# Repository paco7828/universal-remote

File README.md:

# Universal Remote

ESP32-based universal infrared remote control with touch screen.
It can **learn** IR signals, **save them to an SD card**, **resend** them,
and transmit **built-in brand codes**.
The entire UI is touch-controlled, featuring scrollable lists and a virtual
keyboard.

---

## Hardware

| Component | Description |
|-----------|-------------|
| MCU | ESP32 (Using FSPI / SPI2 bus) |
| Display | ILI9341 2.4" TFT, 240x320, portrait (rotation 0) |
| Touch | XPT2046 resistive touch, via SPI |
| Storage | MicroSD card |
| IR Transmitter| TSAL6200 |
| IR Receiver | IRM-3638T |

The display and the SD card use **the same SPI bus** (shared MOSI/MISO/CLK),
multiplexed with CS lines. Before sending an IR signal, the code sets `SD_CS` and `TOUCH_CS`
HIGH to avoid bus conflicts.

### Pinout

| Signal | GPIO |
|--------|------|
| TFT CS | 7 |
| TFT RST | 10 |
| TFT DC | 2 |
| TFT MOSI | 6 |
| TFT MISO | 5 |
| TFT CLK | 4 |
| Touch CS | 8 |
| Touch IRQ | 9 |
| SD CS | 3 |
| IR TX | 0 |
| IR RX | 1 |

---

## Dependencies

- **LovyanGFX** - display + touch driver (ILI9341 + XPT2046)
- **IRremoteESP8266** - IR receive / send / decode
- **Preferences** - ESP32 NVS (for saving themes)
- **SD**, **SPI** - Arduino ESP32 core built-in
- **`./IR-codes.h`** - custom header with built-in Pronto Hex codes
  (EPSON and NEC arrays). **Without this, the project will not compile.**

---

## Features

### Signal learning (Receive)

1. `Signal options -> Receive` starts listening mode.
2. The receiver decodes the signal into `decode_results`.
3. The code accepts a **maximum of 3 frames** at once within a signal
   (`MAX_FRAMES = 3`), measuring the pause between them as `gap_ms`.
4. Repeat frames and identical frames are discarded.
5. An `UNKNOWN` (raw) signal is only accepted if it is the **first** frame,
   and contains at least 10 pulses, filtering out noise.
6. The captured signal type is determined automatically:
   - `SIG_VALUE` - known protocol, fixed-length value (e.g., NEC)
   - `SIG_STATE` - AC-like protocols with byte-array states
   - `SIG_RAW` - unknown, raw microsecond array
7. After capture, a **QWERTY keyboard** appears to name the signal
   (max 25 characters, letters + `-`).
8. Saved to the SD card: `/saved-signals/<group>/<name>.txt`.

### Signal sending (Transmit)

- **Saved signals**: `Signal options -> Transmit` -> group list -> signal list -> Send.
  The group is the part of the signal's name before the `-` (e.g., `TV-power` -> `TV` group).
- **Built-in signals**: `Built-in signals` -> brand -> signal -> Send.
- **Long pressing** the `Send` button repeats the signal (except for `SIG_STATE` signals).
- Transmission strategy:
  - `SIG_VALUE`: `irsend.send(protocol, value, bits)` - for RC5/RC6,
    the toggle bit switches automatically on each new press.
  - `SIG_STATE`: `irsend.send(protocol, state, bytes)`.
  - `SIG_RAW`: `irsend.sendRaw(rawData, len, khz)`.
  - If protocol sending returns `false`, but raw data is available, an
    automatic **raw fallback** occurs.
- For multi-frame signals, there is a `gap_ms` pause between frames.

### Built-in signals

The `IRCode` structures declared in `IR-codes.h` store the codes in Pronto Hex format.
The firmware converts them to raw microsecond arrays using the `prontoToRawSignal()`
function and calculates the carrier frequency with `prontoCarrierKHz()`.

Currently, **only these** are available from the UI in the `hardcodedBrands[]` array:

- EPSON
- NEC

(Other brands will only appear if you add them to the array.)

### SD Card Management

- **Info** - total / free / used space + number of saved signal files.
- **Files** - file browser with directory navigation, size display,
  and individual file deletion (`Del` button, **!NO CONFIRMATION MESSAGE!**).
- **Format** - keeps the `/System Volume Information` and `/built-in-signals`
  directories, deletes everything else.
- File list limit: 500 items.

### UI / Themes

Three selectable color themes (persisted in NVS):

- Futuristic Red (default)
- Futuristic Green
- Futuristic Purple

Theme switching is displayed with an animated spreading circle effect.

Other UI features:

- Boot splash: `UNIVERSAL / REMOTE` text for ~2 seconds.
- **Scrollable lists** with a sprite buffer (`LGFX_Sprite`) to prevent flickering.
- **Double tap** on a list item = open.
- **Long hold** on a repeatable button = rapid fire (`REPEAT_INTERVAL = 200 ms`).
- Maximum number of buttons per screen: **30**.
- Button style: corner accents + scanline pattern.

---

## Navigation Structure

```
Main Menu
├── Signal options
│   ├── Transmit  ->  [Group]  ->  [Signal list]  ->  Send
│   └── Receive   ->  Listening... ->  Captured!   ->  Keyboard -> Save
├── Built-in signals
│   └── [Brand]   ->  [Signal list] ->  Send
├── SD Card options
│   ├── Info
│   ├── Files  ->  browser (Up / Back / Del)
│   └── Format ->  Yes, format / Cancel formatting
└── Change theme
    ├── Futuristic Red
    ├── Futuristic Green
    └── Futuristic Purple
```

If SD initialization fails, "SD Card options" disappears from the main menu.

---

## Saved signal file format

**Not binary** - each signal is a simple, line-separated `.txt` file:

```
# UniRemote IR signal
name: TV-power
carrier_khz: 38
frame: 1
gap_ms: 40
protocol: NEC
bits: 32
value: 0x20DF10EF
length: 68
raw: 9000,4500,560,560,...
frame: 2
...
```

Fields per frame:

- `gap_ms` - pause before the next frame (only if there is a next frame)
- `protocol` - name returned by `typeToString()`
- `bits` - number of bits for `SIG_VALUE`, bytes×8 for `SIG_STATE`
- `value` - hex value (`SIG_VALUE`)
- `bytes` - space-separated hex bytes (`SIG_STATE`)
- `length` + `raw` - raw microsecond array (always saved if available)

When loading the file, the code automatically determines the `kind` based
on the existing fields: value -> state -> raw priority.

Folder structure:

```
/saved-signals/
├── TV/
│   ├── power.txt
│   └── mute.txt
├── Misc/
│   └── random-signal.txt
```

Names without `-` are automatically placed in the `Misc` group.

---

## File structure

| File | Role |
|------|------|
| `UniversalRemote.ino` | Full firmware |
| `IR-codes.h` | Built-in Pronto Hex codes (EPSON, NEC arrays, `IRCode` struct) |

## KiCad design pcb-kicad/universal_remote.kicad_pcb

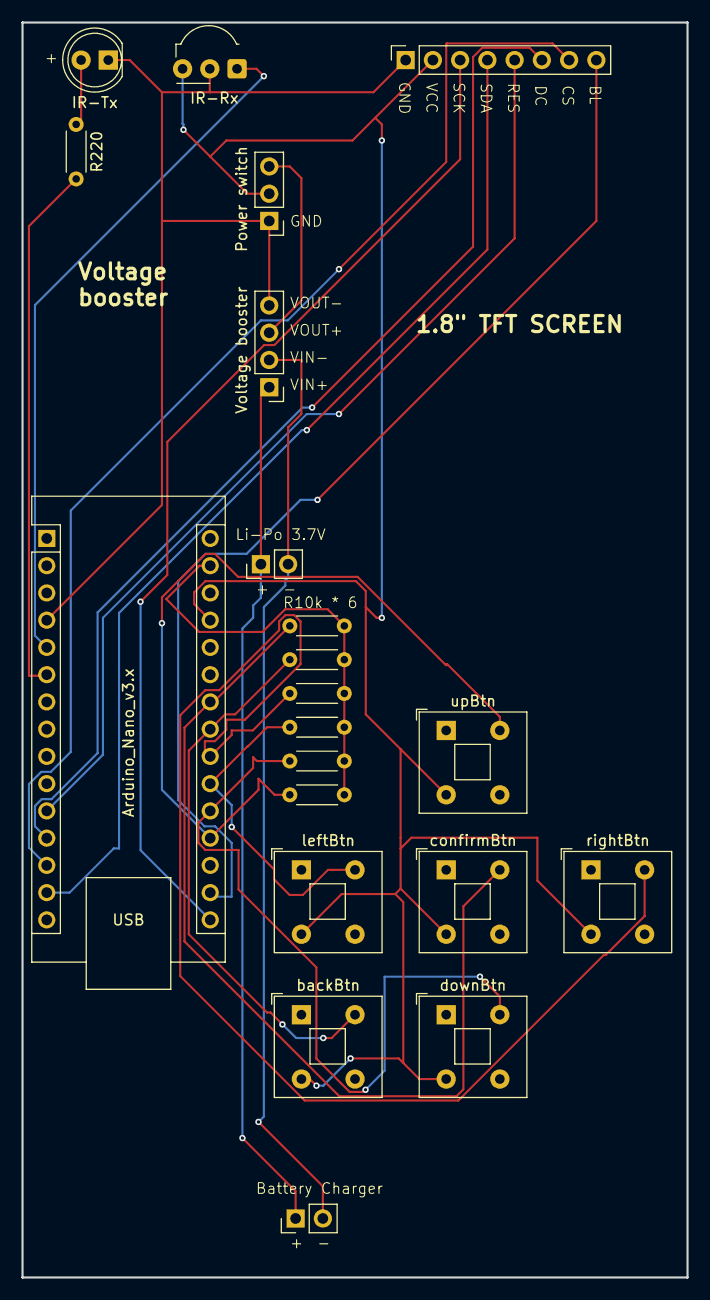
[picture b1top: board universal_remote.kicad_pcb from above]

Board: 2 copper layers, 62.0 x 117.0 mm, 21 parts (0 on the bottom side), 21 nets.

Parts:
A1: Arduino_Nano_v3.x; Arduino_Nano
BT1: Li-Po-3.7V; PinHeader_1x02_P2.54mm_Vertical
IR-Tx: IR-Tx; LED_D5.0mm_IRGrey
J1: 1.8TFT-SCREEN; PinSocket_1x08_P2.54mm_Vertical
J2: Battery charger; PinHeader_1x02_P2.54mm_Vertical
J3: Voltage booster; PinHeader_1x04_P2.54mm_Vertical
J4: Power switch; PinHeader_1x03_P2.54mm_Vertical
R2, R3, R4, R5, R6, R7: 1K; R_Axial_DIN0204_L3.6mm_D1.6mm_P5.08mm_Horizontal
R220: 220; R_Axial_DIN0204_L3.6mm_D1.6mm_P5.08mm_Horizontal
U1: IR-Rx; Vishay_MOLD-3Pin
backBtn: backBtn; SW_Push_2P1T_Toggle_CK_PVA1xxH2xxxxxxV2
confirmBtn: confirmBtn; SW_Push_2P1T_Toggle_CK_PVA1xxH2xxxxxxV2
downBtn: downBtn; SW_Push_2P1T_Toggle_CK_PVA1xxH2xxxxxxV2
leftBtn: leftBtn; SW_Push_2P1T_Toggle_CK_PVA1xxH2xxxxxxV2
rightBtn: rightBtn; SW_Push_2P1T_Toggle_CK_PVA1xxH2xxxxxxV2
upBtn: upBtn; SW_Push_2P1T_Toggle_CK_PVA1xxH2xxxxxxV2

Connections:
unnamed: A1.17 (3V3), J1.8
unnamed: A1.27 (+5V), J1.2, J4.2, U1.3 (Vs), backBtn.3 (B), backBtn.4 (B), confirmBtn.3 (B), confirmBtn.4 (B), downBtn.3 (B), downBtn.4 (B), leftBtn.3 (B), leftBtn.4 (B), rightBtn.3 (B), rightBtn.4 (B), upBtn.3 (B), upBtn.4 (B)
unnamed: A1.19 (A0), R2.2, upBtn.1 (A), upBtn.2 (A)
unnamed: A1.20 (A1), R3.2, downBtn.1 (A), downBtn.2 (A)
unnamed: A1.21 (A2), R4.2, leftBtn.1 (A), leftBtn.2 (A)
unnamed: A1.22 (A3), R5.2, rightBtn.1 (A), rightBtn.2 (A)
unnamed: A1.23 (A4), R6.2, backBtn.1 (A), backBtn.2 (A)
unnamed: A1.24 (A5), R7.2, confirmBtn.1 (A), confirmBtn.2 (A)
unnamed: A1.5 (D2), U1.1 (OUT)
unnamed: A1.6 (D3), R220.2
unnamed: A1.11 (D8), J1.5
unnamed: A1.12 (D9), J1.6
unnamed: A1.13 (D10), J1.7
unnamed: A1.14 (D11), J1.4
unnamed: A1.16 (D13), J1.3
unnamed: A1.29 (GND), R2.1, R3.1, R4.1, R5.1, R6.1, R7.1
unnamed: BT1.1 (+), J2.1, J3.1
unnamed: BT1.2 (-), J2.2, J3.2
unnamed: IR-Tx.2 (A), R220.1
unnamed: A1.4 (GND), IR-Tx.1 (K), J1.1, J3.4, J4.1, U1.2 (GND)
unnamed: J3.3, J4.3

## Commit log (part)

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2024-11-03 Uploaded corrected version of the PCB
    Problems with first version of the PCB:
    -The power switch's positive and negative pin wasn't connected to the microcontroller's circuit
    -The buttons' top left and bottom left pin are connected by default => when button was soldered it was reacting as it was pressed => switched the top left pin to top right at all buttons
2024-11-13 Re-arranged file
2025-01-30 Created UniversalRemote.h which acts as the brain class.
2025-02-01 Fixed callback errors, checkMemory and back to menu works.
2025-02-01 Successfully implemented the memory deletion to the new refactored code.
2025-02-01 Added listen for signal, fix needed, fixed other bugs.
2025-02-02 Added keyboard and functionality, outputText isnt shown correctly, needs fix.
2025-02-02 Fixed keyboard and state errors.
2025-02-02 Added signal storing functionality.
2025-02-02 Backup save for further fixes.
2025-02-02 Fixed checkmemory and memoryFormat functions, saved signals needs fix.
2025-02-02 Modified the listmemorydata so it prints the signal names on serial only.
2025-02-03 Added correct signal saving and outputting, confirmation isnt working at keyboard.
2025-02-03 Fixed signal saving and retrieval and displaying.
2025-02-03 Correct saving, displaying, deleting signals, 2 UI fixes needed and state handlers inside class.
2025-02-03 Renamed and sorted some files.
2025-02-03 Fixed inspectionChoice reset on returning to menu.
2025-02-05 Rearranged file structure and added first version's components.
2025-03-06 Added header v2 with instructions to button usage without resistors to gnd.
2025-03-31 Backup save.
2025-04-03 Added list of components for v3 version.
2025-04-06 Added JST connector to components.
2025-04-13 Added 22 ohm resistors for ch340G D+ and D- data lines.
2025-04-13 Added 12MHz crystal and 2x 22pF capacitors for CH340G.
2025-06-01 Modified V3 components list.
2025-07-01 Fixed errors, removed unnecessary files and parts, added PCB design for V3.
2025-07-01 Changed highlight priority at saved signals page.
2025-07-03 Changed buffer size for larger signals.
2025-07-16 Small fixes for final code.
2025-10-03 Added v4 improvements and IR codes for future use.
2025-10-11 Added v4 version's demo code with freeze functions for esp32 c3 supermini instead of arduino.
2025-10-11 Added components list for v4.
2025-10-11 Added first working demo code without using the class.
2025-10-11 Added ir led strip codes to IR-codes.h.
2025-10-12 Added a futuristic design to the demo code.
2025-10-12 Added v4 menu as txt.
2025-10-12 Rearranged code.
2025-10-12 Added functions for correct compiling.
2025-10-12 Added basic menu options and their options too for display.
2025-10-12 Fixed code's compilation errors and projector brands' options' height.
2025-10-12 Added border for footer and changed title to universal remote.
2025-10-12 Optimized code with repetitions removed.
2025-10-12 Rearranged code with big comments.
2025-10-12 Fixed compile errors.
2025-10-12 Added grid creator function and styled back button so it stands out from the general buttons.
2025-10-12 Added transmit and receive options to be shown.
2025-10-12 Added correct spacing for transmit and receive options and sd card options.
2025-10-13 Added touch button debounce and titles. Removed backToMenu and changed to drawMenuUI.
2025-10-13 Modified built-in IR code structure and added serial logging as a demo for the projector brands.
2025-10-13 Added real SD card info to the corresponding place.
2025-10-13 Added initialization without SD card so SD card options aren't available. Back button has been inserted to listSDInfo function with new drawBackBtn.
2025-10-13 Added actual SD card formatting with folder exception.
2025-10-15 Updated SS14 with 1N5819HW-7-F in components list.
2025-10-26 Added v4 gerber files.
2025-10-26 Added new gerber files with enclosure.
2025-10-26 Added universal-remote enclosure v1.
2025-10-26 ADded signature and project name to pcb.
2025-11-10 Added all of the new functions for the v4, backup save, optimization and re-check needed.
2025-11-11 Backup save for new implementations, review and optimization needed.
2025-11-14 Added v1 shell.
2025-12-25 Added saved signals grouping logic.
2025-12-25 Added File deletion logic while inspecting SD card files.
2025-12-26 Increased array sizes and viewable file count in SD file browsing mode.
2025-12-26 Added optimized drawing and loading logic to saved signals transmission list and built in signals list. Moved up the arrow pointing downwards in the SD File browser.
2026-01-27 Fixed grouping logic.
2026-06-08 Revise README for ESP32 universal IR remote
    Updated README to reflect new features and hardware details for the ESP32-based universal IR remote.
2026-06-08 Added v4 assembled device images.
2026-06-16 Added V5 demo code and pcb.
2026-06-23 Added V5 code with new touch features and better space usage.
2026-06-26 Fixed mosfet orientation for v5 pcb
2026-06-27 Changed 2.2R resistor to 10R resistor at v5 pcb.
